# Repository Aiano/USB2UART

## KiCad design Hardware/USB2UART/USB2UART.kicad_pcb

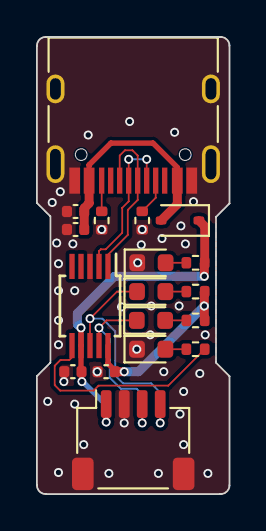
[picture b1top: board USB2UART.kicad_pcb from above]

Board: 2 copper layers, 10.7 x 25.4 mm, 18 parts (0 on the bottom side), 15 nets.

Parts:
C1, C3, C4: 100nF; C_0402_1005Metric
C2: 1uF; C_0402_1005Metric
D1: 1N5819WS; D_SOD-323
D2, D3, D4, D5: LED; LED_0603_1608Metric
J1: Conn_01x04_MountingPin; JST_SH_SM04B-SRSS-TB_1x04-1MP_P1.00mm_Horizontal
J2: USB_C_Receptacle_USB2.0; USB_C_Receptacle_HRO_TYPE-C-31-M-12
R1, R2: 5.1k; R_0402_1005Metric
R3, R4: 470R; R_0402_1005Metric
R5: 1k; R_0402_1005Metric
R6: 10k; R_0402_1005Metric
U1: CH340E; MSOP-10_3x3mm_P0.5mm

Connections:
+3V3: C4.1, R3.2, R4.2, U1.10 (V3)
+5V: C3.1, D1.1 (K), J1.1, R6.2, U1.7 (VCC)
/MCU_RX: D2.1 (K), J1.4, U1.8 (TXD)
/MCU_TX: D3.1 (K), J1.3, U1.9 (RXD)
/TNOW: R5.2, U1.6 (TNOW)
/USB_DN: J2.A7 (D-), J2.B7 (D-), U1.2 (UD-)
/USB_DP: J2.A6 (D+), J2.B6 (D+), U1.1 (UD+)
GND: C1.2, C2.2, C3.2, C4.2, D4.1 (K), D5.1 (K), J1.2, J1.MP (MountPin), J2.A1 (GND), J2.A12 (GND), J2.B1 (GND), J2.B12 (GND), J2.S1 (SHIELD), R1.2, R2.2, U1.3 (GND)
unnamed: D2.2 (A), R3.1
unnamed: D3.2 (A), R4.1
unnamed: D4.2 (A), R5.1
unnamed: D5.2 (A), R6.1
unnamed: J2.A5 (CC1), R2.1
unnamed: J2.B5 (CC2), R1.1
VBUS: C1.1, C2.1, D1.2 (A), J2.A4 (VBUS), J2.A9 (VBUS), J2.B4 (VBUS), J2.B9 (VBUS)
